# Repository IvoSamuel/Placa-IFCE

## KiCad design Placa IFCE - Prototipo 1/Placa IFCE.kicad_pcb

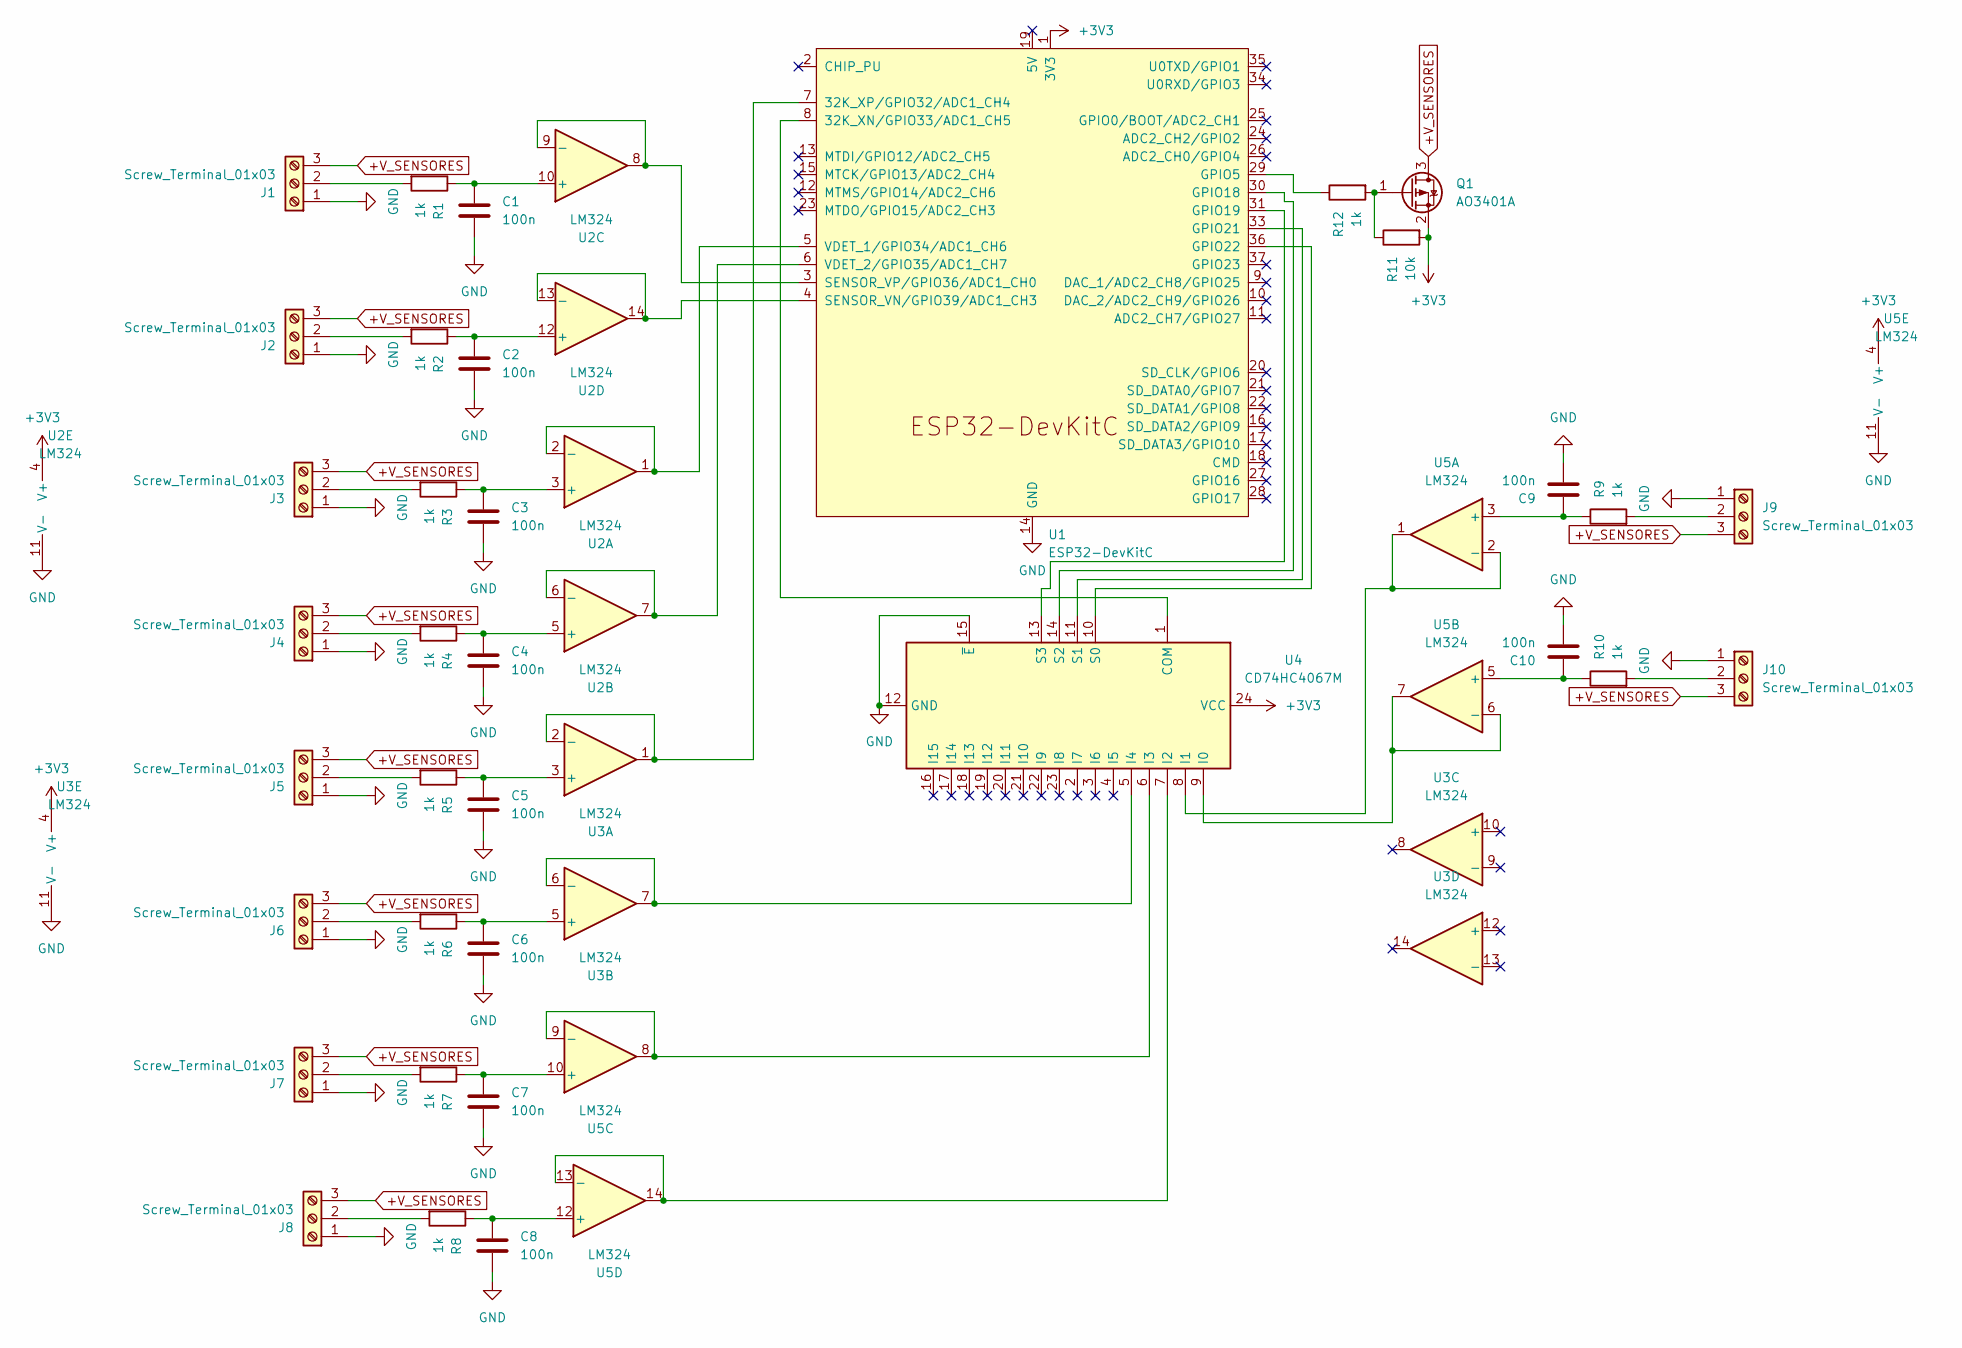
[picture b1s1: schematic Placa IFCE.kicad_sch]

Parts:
C1, C2, C3, C4, C5, C6, C7, C8, C9, C10: 100n; C_Disc_D5.0mm_W2.5mm_P5.00mm
J1, J2, J3, J4, J5, J6, J7, J8, J9, J10: Screw_Terminal_01x03; TerminalBlock_Phoenix_MKDS-1,5-3-5.08_1x03_P5.08mm_Horizont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
Q1: AO3401A; TO-220-3_Vertical
R1, R2, R3, R4, R5, R6, R7, R8, R9, R10, R12: 1k; R_Axial_DIN0207_L6.3mm_D2.5mm_P7.62mm_Horizontal
R11: 10k; R_Axial_DIN0207_L6.3mm_D2.5mm_P7.62mm_Horizontal
U1: ESP32-DevKitC
U2, U3, U5: LM324; DIP-14_W7.62mm_LongPads
U4: CD74HC4067M; DIP-24_W15.24mm_LongPads

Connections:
+3V3: Q1.2 (S), R11.2, U1.1 (3V3), U2.4 (V+), U3.4 (V+), U4.24 (VCC), U5.4 (V+)
+V_SENSORES: J1.3, J2.3, J3.3, J4.3, J5.3, J6.3, J7.3, J8.3, J9.3, J10.3, Q1.3 (D)
GND: C1.1, C2.1, C3.1, C4.1, C5.1, C6.1, C7.1, C8.1, C9.1, C10.1, J1.1, J2.1, J3.1, J4.1, J5.1, J6.1, J7.1, J8.1, J9.1, J10.1, U1.14 (GND), U1.32 (GND), U1.38 (GND), U2.11 (V-), U3.11 (V-), U4.12 (GND), U4.15 (~E), U5.11 (V-)
unnamed: J1.2, R1.2
unnamed: J2.2, R2.2
unnamed: J3.2, R3.2
unnamed: J4.2, R4.2
unnamed: J5.2, R5.2
unnamed: J6.2, R6.2
unnamed: J7.2, R7.2
unnamed: J8.2, R8.2
unnamed: J9.2, R9.2
unnamed: J10.2, R10.2
unnamed: Q1.1 (G), R11.1, R12.2
unnamed: U1.8 (32K_XN/GPIO33/ADC1_CH5), U4.1 (COM)
unnamed: U1.7 (32K_XP/GPIO32/ADC1_CH4), U3.1, U3.2 (-)
unnamed: R12.1, U1.29 (GPIO5)
unnamed: U1.30 (GPIO18), U4.14 (S2)
unnamed: U1.31 (GPIO19), U4.13 (S3)
unnamed: U1.33 (GPIO21), U4.11 (S1)
unnamed: U1.36 (GPIO22), U4.10 (S0)
unnamed: U1.4 (SENSOR_VN/GPIO39/ADC1_CH3), U2.13 (-), U2.14
unnamed: U1.3 (SENSOR_VP/GPIO36/ADC1_CH0), U2.8, U2.9 (-)
unnamed: U1.5 (VDET_1/GPIO34/ADC1_CH6), U2.1, U2.2 (-)
unnamed: U1.6 (VDET_2/GPIO35/ADC1_CH7), U2.6 (-), U2.7
unnamed: C3.2, R3.1, U2.3 (+)
unnamed: C4.2, R4.1, U2.5 (+)
unnamed: C1.2, R1.1, U2.10 (+)
unnamed: C2.2, R2.1, U2.12 (+)
unnamed: C5.2, R5.1, U3.3 (+)
unnamed: C6.2, R6.1, U3.5 (+)
unnamed: U3.6 (-), U3.7, U4.5 (I4)
unnamed: U4.9 (I0), U5.6 (-), U5.7
unnamed: U4.8 (I1), U5.1, U5.2 (-)
unnamed: U4.7 (I2), U5.13 (-), U5.14
unnamed: U4.6 (I3), U5.8, U5.9 (-)
unnamed: C9.2, R9.1, U5.3 (+)
unnamed: C10.2, R10.1, U5.5 (+)
unnamed: C7.2, R7.1, U5.10 (+)
unnamed: C8.2, R8.1, U5.12 (+)

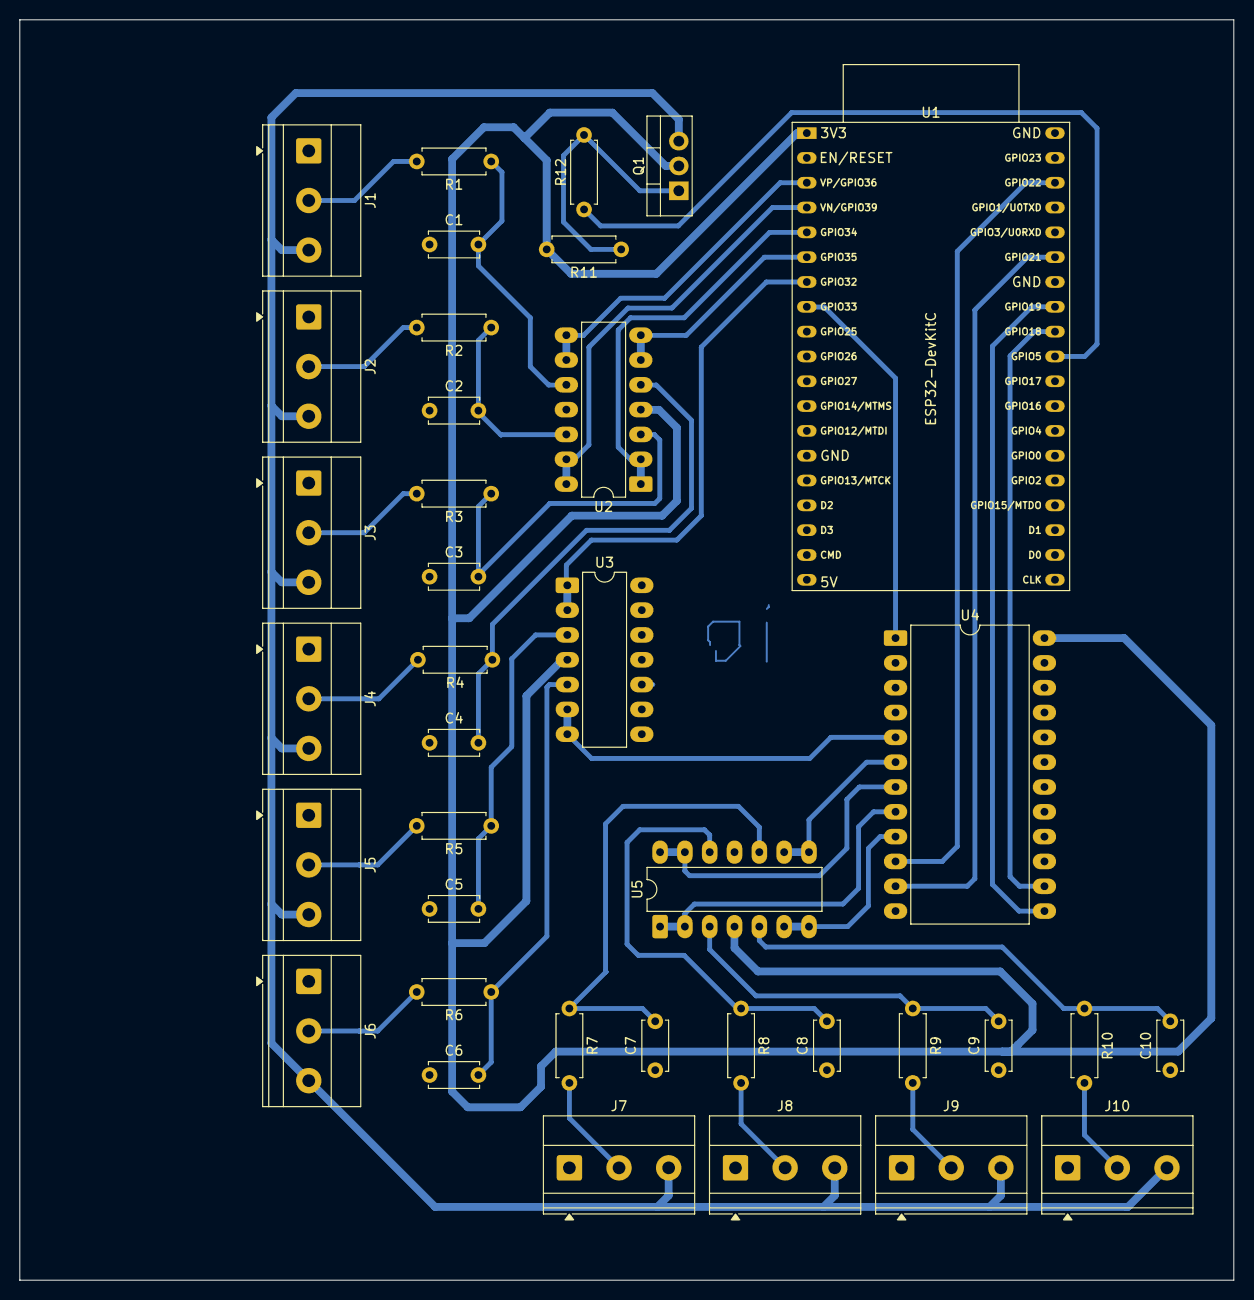
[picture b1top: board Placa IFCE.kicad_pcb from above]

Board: 2 copper layers, 124.2 x 129.0 mm, 38 parts (0 on the bottom side), 40 nets.
